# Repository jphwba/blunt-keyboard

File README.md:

# Blunt-Keyboard

This keyboard is a 75% keyboard which has a magnetically attatchable numpad to it. It uses a raspberry pi pico rp2040 as the microcontroller for the main keyboard while using a xiao seeed studio rp2040 as the microcontroller for the numpad. This would connect via two usb C cables into my pc. I made this because I really need a new keyboard since my current one cant even play games anymore due to some weird bug in the pcb where it just randomly spams keys, plus I've had it for almost 10 years.

## Assembly
On the main part of the keyboard, the pcb is mounted using five mounting holes on the pcb and five standoffs on the base where M2 heatset inserts will sit. On top of these standoffs will go the PCB where it will be screwed into the base. Then the top goes ontop of the pcb/base walls. This is connected via screws going from the bottom to the top
The numpad however is screwed in with the threads in the 3d print. This was not a great design choice at the time as I wasn't as experienced with how 3d printers work but I will take the gamble and if it doesn't work I am able to use tape. HOWEVER the pcb is screwed into the base using the same heatset inserts so the pcb will be secured. The key plate is attatched to the top cover with a joint (i forgot the name).
For the magnetic attatchements, two 7mm magnets go in two the 7mm wide holes on BOTH the numpad and the main keyboard and is attatched to each part with some basic super glue. With this the two devices can seamlessly attatch and detach. The two components also have seperate microcontrollers, meaning two different usb connections into my pc. I chose this over having the numpad atatch into the main keyboard for first simple firmware and schematic design but also because it means I have a portable numpad.

### Numpad Render

### Main Keyboard Render

### Full Assembled Render

### PCB Layout Pad

### Pad Schematic

### Main PCB Layout

### Main Schematic

### Main PCB Order

### PAD PCB Order

### BOM
|Item                                                                                                                                                                          |Qty|Price (AUD)|Site                                                                                                                                                                                                                                                                                                                                                                                                                                                                                                                                                                                                                                 |
|------------------------------------------------------------------------------------------------------------------------------------------------------------------------------|---|-----------|-------------------------------------------------------------------------------------------------------------------------------------------------------------------------------------------------------------------------------------------------------------------------------------------------------------------------------------------------------------------------------------------------------------------------------------------------------------------------------------------------------------------------------------------------------------------------------------------------------------------------------------|
|DUROCK Plate Mount Stabilizers V3, Innovative Pre-clipped Stem for Minimum Wire Wobble 2U 6.25U 7U Plate Keyboard Stabilizers V3 (Color: V3 BS 4x2u 1x6.25u)                  |1  |$11.39     |https://www.aliexpress.com/item/1005006528731543.html?spm=a2g0o.cart.0.0.4c3438dal21w6q&mp=1&pdp_npi=6%40dis%21AUD%21AUD+11.39%21AUD+11.39%21%21AUD+11.39%21%21%21%402103129017855613570607710e1021%2112000037543723481%21ct%21AU%21-1%21%211%210%21&pdp_ext_f=%7B%22cart2PdpParams%22%3A%7B%22pdpBusinessMode%22%3A%22retail%22%7D%7D                                                                                                                                                                                                                                                                                               |
|110Pcs Outemu Switches for Mechanical Keyboard 3Pin Clicky Linear Tactile Silent Switch RGB LED SMD Gaming Mechan with MX Switch (Color: 110p DustProof Brown)                |1  |$43.46     |https://www.aliexpress.com/item/1005011976942889.html?spm=a2g0o.cart.0.0.4c3438dal21w6q&mp=1&pdp_npi=6%40dis%21AUD%21AUD+43.46%21AUD+3.08%21%21AUD+3.08%21%21%21%402103129017855613570607710e1021%2112000057186154978%21ct%21AU%21-1%21%211%210%21                                                                                                                                                                                                                                                                                                                                                                                   |
|100pcs/lot 1N4148W T4 BAV21W T3 SOD-123 1N4148WS BAV21WS SOD-323 1N4148WT SOD-523 1N4148 BAV21 BAV21W SMD Switching Diodes (Color: 1N4148W T4 SOD-123)                        |1  |$3.72      |https://www.aliexpress.com/item/1005007160563285.html?spm=a2g0o.cart.0.0.4c3438dal21w6q&mp=1&pdp_npi=6%40dis%21AUD%21AUD+3.72%21AUD+2.27%21%21AUD+2.27%21%21%21%402103129017855613570607710e1021%2112000039653324544%21ct%21AU%21-1%21%211%210%21                                                                                                                                                                                                                                                                                                                                                                                    |
|Original Raspberry Pi Pico Development Board,Pico or Pico H with Pin Header, support MciroPython/C++                                                                          |1  |$9.78      |https://www.aliexpress.com/item/1005008714908011.html?spm=a2g0o.cart.0.0.4c3438dal21w6q&mp=1&pdp_npi=6%40dis%21AUD%21AUD+9.78%21AUD+4.79%21%21AUD+4.79%21%21%21%402103129017855613570607710e1021%2112000046359830441%21ct%21AU%21-1%21%211%210%21                                                                                                                                                                                                                                                                                                                                                                                    |
|100PCS SK6812MINI-E SK6812 MINI-E RGB 3228 LED chip SMD                                                                                                                       |1  |$14.24     |https://www.aliexpress.com/item/1005005956813491.html?spm=a2g0o.cart.0.0.2cd238daWuNwsJ&mp=1&pdp_npi=6%40dis%21AUD%21AUD+14.24%21AUD+13.39%21%21AUD+13.39%21%21%21%40210328df17855654955145397e10b6%2112000035024278716%21ct%21AU%21-1%21%211%210%21                                                                                                                                                                                                                                                                                                                                                                                 |
|XVX 119 Keys Black Transparent PC Keycaps 60/68/75/87/98/100 Mechanical Keyboard Key Cap Crystal Clear Keycaps for Gaming/Office (Color: black)                               |1  |$30.84     |https://www.aliexpress.com/item/1005010587844811.html?spm=a2g0o.cart.0.0.675938daAlDdi5&mp=1&pdp_npi=6%40dis%21AUD%21AUD+30.95%21AUD+22.59%21%21AUD+22.59%21%21%21%40210328df17855662600466416e0d9f%2112000052907539638%21ct%21AU%21-1%21%211%210%21                                                                                                                                                                                                                                                                                                                                                                                 |
|50pcs 5-30mm Anti-slip Black Self Adhesive Round Silicone Rubber Feet Pad Laptops Keyboards Calculators Monitors Anti-skid Pads (Size: OD 15mm, Color: Thick 0.5mm)           |1  |$3.25      |https://www.aliexpress.com/item/1005012365785428.html?spm=a2g0o.productlist.main.9.4de19oaH9oaHuB&algo_pvid=cd5a83e3-1229-4647-a495-e3f16f297cca&algo_exp_id=cd5a83e3-1229-4647-a495-e3f16f297cca-8&pdp_ext_f=%7B%22order%22%3A%2210%22%2C%22eval%22%3A%221%22%2C%22fromPage%22%3A%22search%22%7D&pdp_npi=6%40dis%21AUD%212.31%212.31%21%21%211.60%211.60%21%4021030f4a17855681020947549e1149%2112000058187329086%21sea%21AU%210%21ABX%211%210%21n_tag%3A-29910%3Bd%3Aa8aafb62%3Bm03_new_user%3A-29895&curPageLogUid=XU7lr6tnileh&utparam-url=scene%3Asearch%7Cquery_from%3A%7Cx_object_id%3A1005012365785428%7C_p_origin_prod%3A    |
|10/15/20/40/50/100pcs M1 M1.2 M1.4 M2 M2.5 M3 M4 M5 M6 M8 Thread Knurled Brass Heat Insert Nut Copper Embedment Embed Parts Nuts (Size: M2x3.5mm (50pcs), Color: Length 3.5mm)|1  |$3.87      |https://www.aliexpress.com/item/1005007424930348.html?spm=a2g0o.productlist.main.1.5d47dkVRdkVRFI&algo_pvid=f3287ffa-e8c5-45b6-be15-06364e1b8824&algo_exp_id=f3287ffa-e8c5-45b6-be15-06364e1b8824-0&pdp_ext_f=%7B%22order%22%3A%224489%22%2C%22eval%22%3A%221%22%2C%22fromPage%22%3A%22search%22%7D&pdp_npi=6%40dis%21AUD%212.44%211.46%21%21%2111.44%216.86%21%402101d2e717859226917101841e10da%2112000040708235172%21sea%21AU%210%21ABX%211%210%21n_tag%3A-29910%3Bd%3Aa8aafb62%3Bm03_new_user%3A-29895&curPageLogUid=nWZkAVTMulic&utparam-url=scene%3Asearch%7Cquery_from%3A%7Cx_object_id%3A1005007424930348%7C_p_origin_prod%3A |
|7x3 mm Powerful Magnets 7mmx3mm Small Round Magnet 7x3mm For Home Refrigerators, Offices DIY 7*3 mm (Color: 20PCS, Size: 7x3mm)                                               |1  |$9.70      |https://www.aliexpress.com/item/1005009743408781.html?spm=a2g0o.cart.0.0.5a4038dapRSJXy&mp=1&pdp_npi=6%40dis%21AUD%21AUD+9.70%21AUD+6.89%21%21AUD+6.89%21%21%21%402101ca9517859231451535510e2109%2112000050016793430%21ct%21AU%21-1%21%211%210%21                                                                                                                                                                                                                                                                                                                                                                                    |
|Pad Specific                                                                                                                                                                  |   |           |                                                                                                                                                                                                                                                                                                                                                                                                                                                                                                                                                                                                                                     |
|(50pcs) 1N4148W T4 4148WS 4148WT SOD-123/SOD-323/SOD-523 SMD Switching Diodes (Color: 1N4148W T4 SOD123)                                                                      |1  |$0.88      |https://www.aliexpress.com/item/1005007406908801.html?spm=a2g0o.cart.0.0.2cd238daUQg641&mp=1&pdp_npi=6%40dis%21AUD%21AUD+0.88%21AUD+0.88%21%21AUD+0.88%21%21%21%40210328df17855654453944118e10b6%2112000044783709518%21ct%21AU%21-1%21%211%210%21                                                                                                                                                                                                                                                                                                                                                                                    |
|10pcs/1pc RP2040 Seeed XIAO Raspberry Pi Development Board Module For Arduino/MicroPython/CircuitPython (Model Number: 1pc)                                                   |1  |$10.70     |https://www.aliexpress.com/item/1005008200917480.html?spm=a2g0o.productlist.main.1.6ac5379cKx7D6w&algo_pvid=b6c6bc21-d979-4d64-972b-8bcf0e8f28f7&algo_exp_id=b6c6bc21-d979-4d64-972b-8bcf0e8f28f7-0&pdp_ext_f=%7B%22order%22%3A%22279%22%2C%22eval%22%3A%221%22%2C%22fromPage%22%3A%22search%22%7D&pdp_npi=6%40dis%21AUD%2120.56%2114.39%21%21%2114.23%219.96%21%402101e81117855657959013083e100a%2112000058130698584%21sea%21AU%210%21ABX%211%210%21n_tag%3A-29910%3Bd%3Aa8aafb62%3Bm03_new_user%3A-29895&curPageLogUid=Gb0bLHPVv7Jw&utparam-url=scene%3Asearch%7Cquery_from%3A%7Cx_object_id%3A1005008200917480%7C_p_origin_prod%3A|
|Printing-Legion                                                                                                                                                               |1  |$30.00     |                                                                                                                                                                                                                                                                                                                                                                                                                                                                                                                                                                                                                                     |
|Total                                                                                                                                                                         |   |$141.83    |                                                                                                                                                                                                                                                                                                                                                                                                                                                                                                                                                                                                                                     |

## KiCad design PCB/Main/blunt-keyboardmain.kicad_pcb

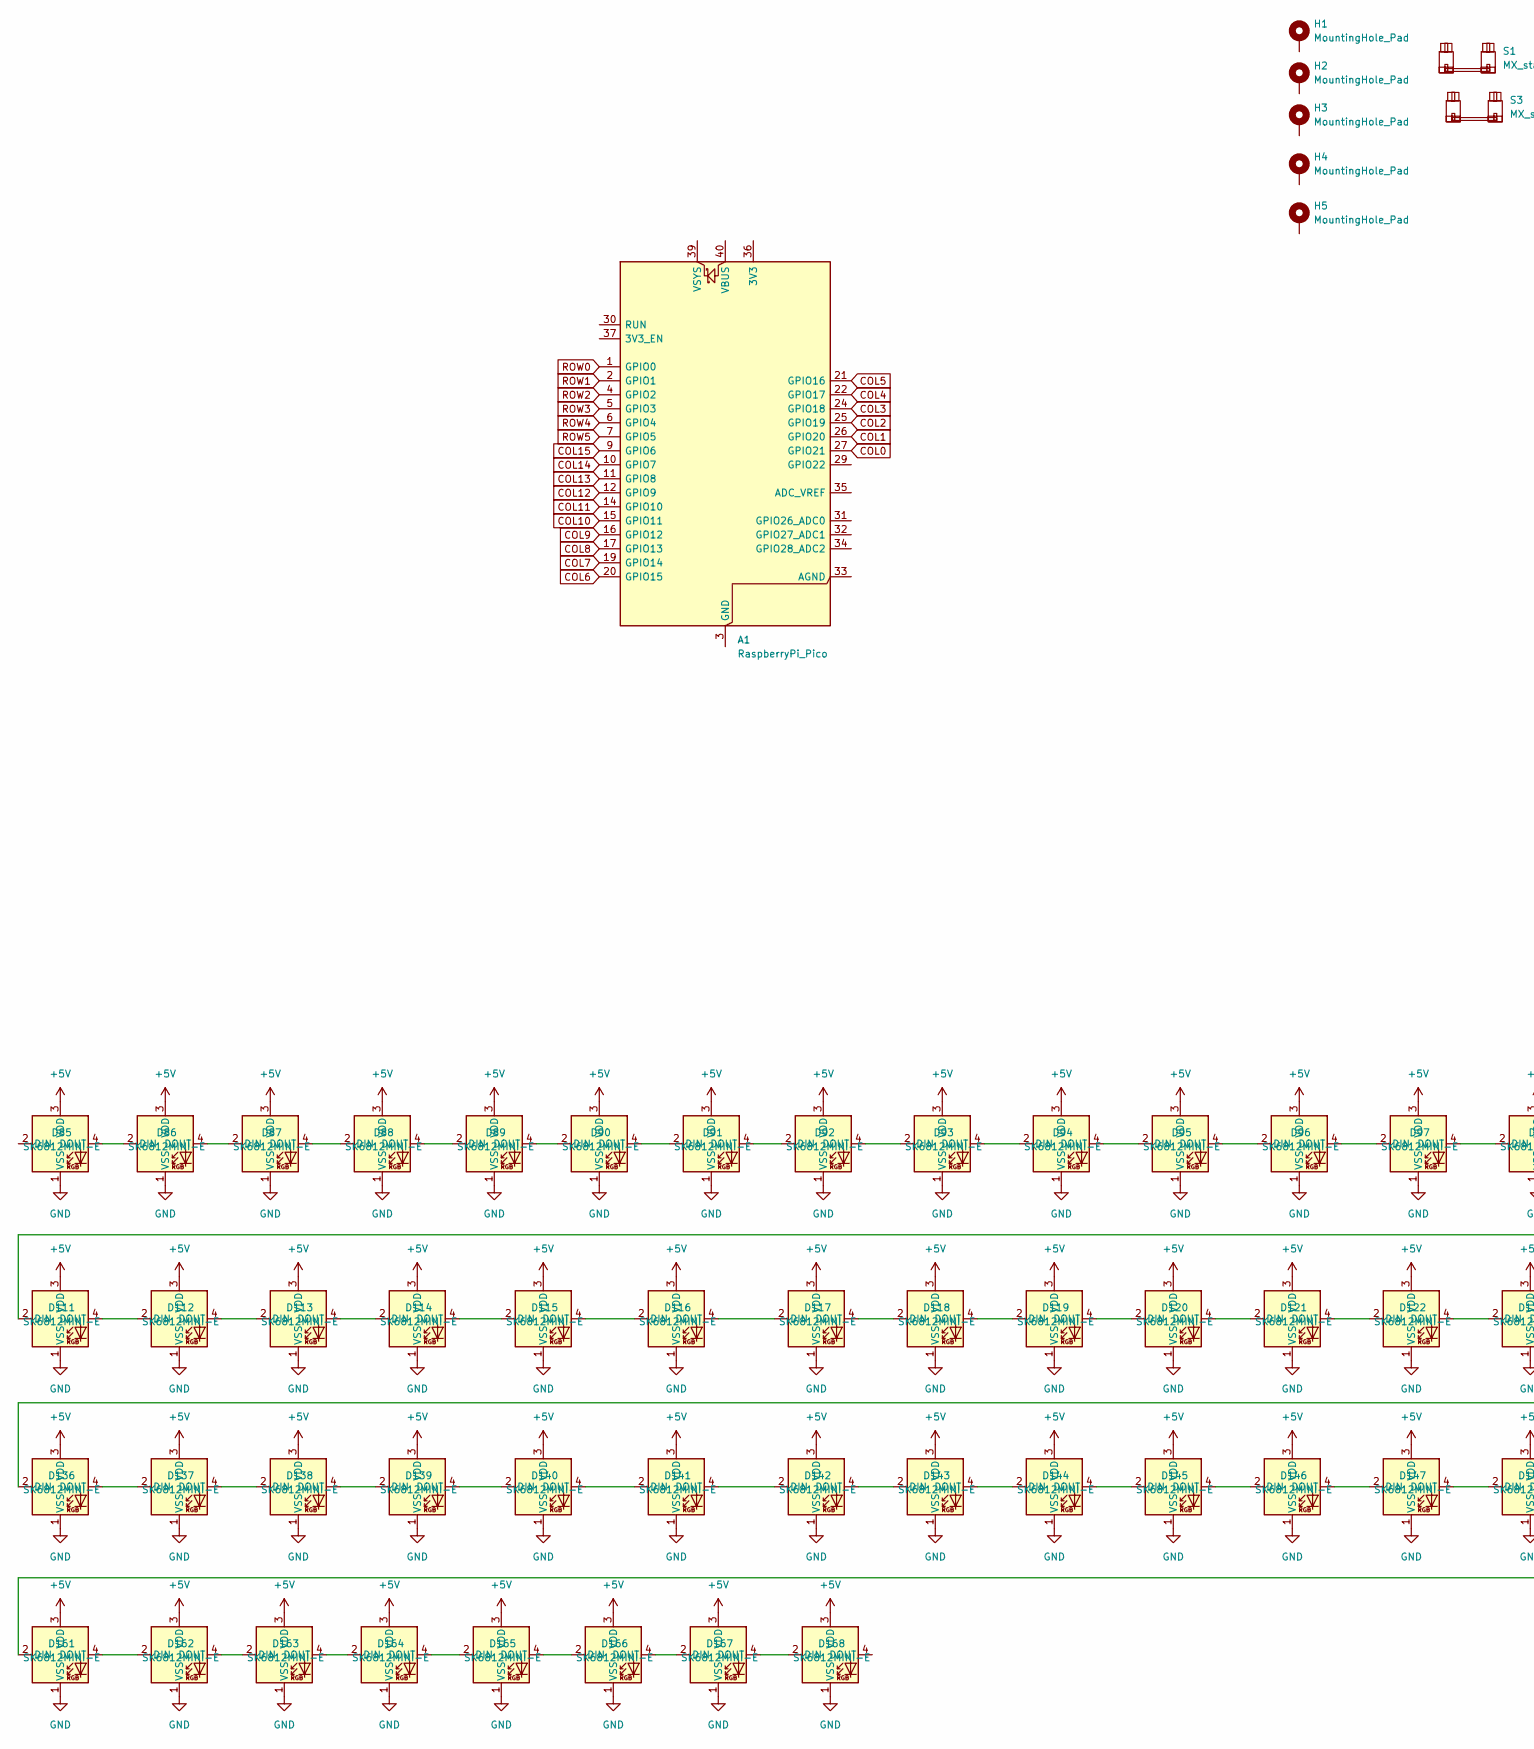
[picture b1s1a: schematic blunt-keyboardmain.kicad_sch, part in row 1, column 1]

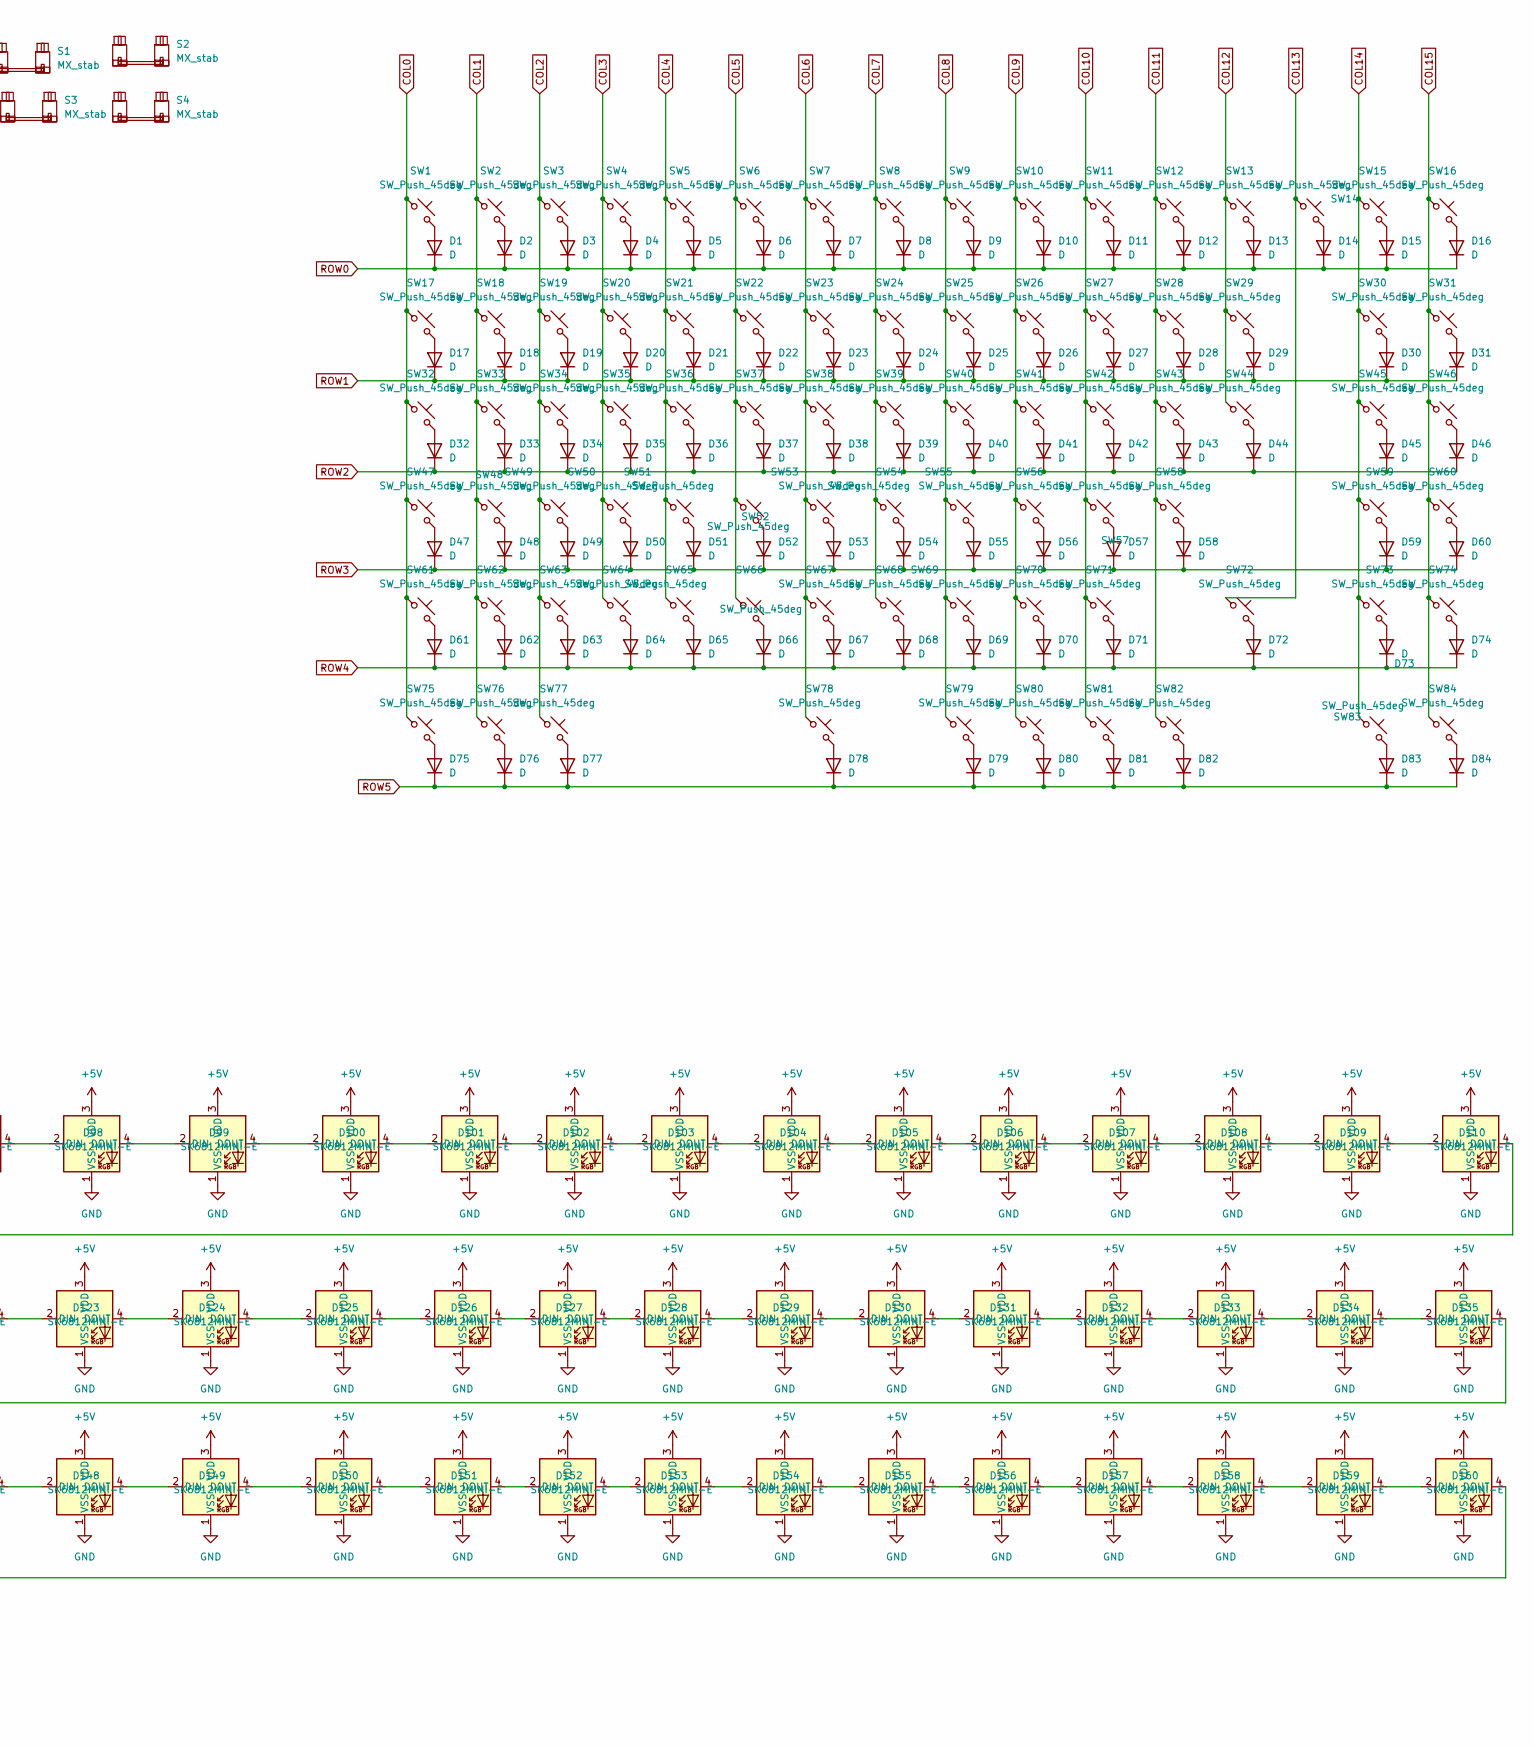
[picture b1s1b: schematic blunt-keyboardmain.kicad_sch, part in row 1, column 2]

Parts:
A1: RaspberryPi_Pico; RaspberryPi_Pico_Common_Unspecified
D1, D2, D3, D4, D5, D6, D7, D8, D9, D10, D11, D12, D13, D14, D15, D16, D17, D18, D19, D20, D21, D22, D23, D24, D25, D26, D27, D28, D29, D30, D31, D32, D33, D34, D35, D36, D37, D38, D39, D40, D41, D42, D43, D44, D45, D46, D47, D48, D49, D50, D51, D52, D53, D54, D55, D56, D57, D58, D59, D60, D61, D62, D63, D64, D65, D66, D67, D68, D69, D70, D71, D72, D73, D74, D75, D76, D77, D78, D79, D80, D81, D82, D83, D84: D; D_SOD-123
D85, D86, D87, D88, D89, D90, D91, D92, D93, D94, D95, D96, D97, D98, D99, D100, D101, D102, D103, D104, D105, D106, D107, D108, D109, D110, D111, D112, D113, D114, D115, D116, D117, D118, D119, D120, D121, D122, D123, D124, D125, D126, D127, D128, D129, D130, D131, D132, D133, D134, D135, D136, D137, D138, D139, D140, D141, D142, D143, D144, D145, D146, D147, D148, D149, D150, D151, D152, D153, D154, D155, D156, D157, D158, D159, D160, D161, D162, D163, D164, D165, D166, D167, D168: SK6812MINI-E; LED_SK6812MINI-E_3.2x2.8mm_P1.5mm_ReverseMount
H1, H2, H3, H4, H5: MountingHole_Pad; MountingHole_2.2mm_M2_ISO7380_Pad
S1: MX_stab; STAB_MX_P_6.25u
S2, S4: MX_stab; STAB_MX_P_2.25u
S3: MX_stab; STAB_MX_P_2u
SW1, SW2, SW3, SW4, SW5, SW6, SW7, SW8, SW9, SW10, SW11, SW12, SW13, SW14, SW15, SW16, SW17, SW18, SW19, SW20, SW21, SW22, SW23, SW24, SW25, SW26, SW27, SW28, SW29, SW30, SW31, SW33, SW34, SW35, SW36, SW37, SW38, SW39, SW40, SW41, SW42, SW43, SW44, SW46, SW48, SW49, SW50, SW51, SW52, SW53, SW54, SW55, SW56, SW57, SW58, SW60, SW61, SW62, SW63, SW64, SW65, SW66, SW67, SW68, SW69, SW70, SW71, SW73, SW74, SW78, SW79, SW80, SW81, SW82, SW83, SW84: SW_Push_45deg; SW_Matias_1.00u
SW32, SW45: SW_Push_45deg; SW_Matias_1.50u
SW47, SW72: SW_Push_45deg; SW_Matias_1.75u
SW59: SW_Push_45deg; SW_Matias_2.25u
SW75, SW76, SW77: SW_Push_45deg; SW_Matias_1.25u

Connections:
+5V: D85.3 (VDD), D86.3 (VDD), D87.3 (VDD), D88.3 (VDD), D89.3 (VDD), D90.3 (VDD), D91.3 (VDD), D92.3 (VDD), D93.3 (VDD), D94.3 (VDD), D95.3 (VDD), D96.3 (VDD), D97.3 (VDD), D98.3 (VDD), D99.3 (VDD), D100.3 (VDD), D101.3 (VDD), D102.3 (VDD), D103.3 (VDD), D104.3 (VDD), D105.3 (VDD), D106.3 (VDD), D107.3 (VDD), D108.3 (VDD), D109.3 (VDD), D110.3 (VDD), D111.3 (VDD), D112.3 (VDD), D113.3 (VDD), D114.3 (VDD), D115.3 (VDD), D116.3 (VDD), D117.3 (VDD), D118.3 (VDD), D119.3 (VDD), D120.3 (VDD), D121.3 (VDD), D122.3 (VDD), D123.3 (VDD), D124.3 (VDD), D125.3 (VDD), D126.3 (VDD), D127.3 (VDD), D128.3 (VDD), D129.3 (VDD), D130.3 (VDD), D131.3 (VDD), D132.3 (VDD), D133.3 (VDD), D134.3 (VDD), D135.3 (VDD), D136.3 (VDD), D137.3 (VDD), D138.3 (VDD), D139.3 (VDD), D140.3 (VDD), D141.3 (VDD), D142.3 (VDD), D143.3 (VDD), D144.3 (VDD), D145.3 (VDD), D146.3 (VDD), D147.3 (VDD), D148.3 (VDD), D149.3 (VDD), D150.3 (VDD), D151.3 (VDD), D152.3 (VDD), D153.3 (VDD), D154.3 (VDD), D155.3 (VDD), D156.3 (VDD), D157.3 (VDD), D158.3 (VDD), D159.3 (VDD), D160.3 (VDD), D161.3 (VDD), D162.3 (VDD), D163.3 (VDD), D164.3 (VDD), D165.3 (VDD), D166.3 (VDD), D167.3 (VDD), D168.3 (VDD)
COL0: A1.27 (GPIO21), SW1.1, SW17.1, SW32.1, SW47.1, SW61.1, SW75.1
COL1: A1.26 (GPIO20), SW2.1, SW18.1, SW33.1, SW48.1, SW62.1, SW76.1
COL2: A1.25 (GPIO19), SW3.1, SW19.1, SW34.1, SW49.1, SW63.1, SW77.1
COL3: A1.24 (GPIO18), SW4.1, SW20.1, SW35.1, SW50.1, SW64.1
COL4: A1.22 (GPIO17), SW5.1, SW21.1, SW36.1, SW51.1, SW65.1
COL5: A1.21 (GPIO16), SW6.1, SW22.1, SW37.1, SW52.1, SW66.1
COL6: A1.20 (GPIO15), SW7.1, SW23.1, SW38.1, SW53.1, SW67.1, SW78.1
COL7: A1.19 (GPIO14), SW8.1, SW24.1, SW39.1, SW54.1, SW68.1
COL8: A1.17 (GPIO13), SW9.1, SW25.1, SW40.1, SW55.1, SW69.1, SW79.1
COL9: A1.16 (GPIO12), SW10.1, SW26.1, SW41.1, SW56.1, SW70.1, SW80.1
COL10: A1.15 (GPIO11), SW11.1, SW27.1, SW42.1, SW57.1, SW71.1, SW81.1
COL11: A1.14 (GPIO10), SW12.1, SW28.1, SW43.1, SW58.1, SW82.1
COL12: A1.12 (GPIO9), SW13.1, SW29.1, SW44.1
COL13: A1.11 (GPIO8), SW14.1, SW72.1
COL14: A1.10 (GPIO7), SW15.1, SW30.1, SW45.1, SW59.1, SW73.1, SW83.1
COL15: A1.9 (GPIO6), SW16.1, SW31.1, SW46.1, SW60.1, SW74.1, SW84.1
GND: D85.1 (VSS), D86.1 (VSS), D87.1 (VSS), D88.1 (VSS), D89.1 (VSS), D90.1 (VSS), D91.1 (VSS), D92.1 (VSS), D93.1 (VSS), D94.1 (VSS), D95.1 (VSS), D96.1 (VSS), D97.1 (VSS), D98.1 (VSS), D99.1 (VSS), D100.1 (VSS), D101.1 (VSS), D102.1 (VSS), D103.1 (VSS), D104.1 (VSS), D105.1 (VSS), D106.1 (VSS), D107.1 (VSS), D108.1 (VSS), D109.1 (VSS), D110.1 (VSS), D111.1 (VSS), D112.1 (VSS), D113.1 (VSS), D114.1 (VSS), D115.1 (VSS), D116.1 (VSS), D117.1 (VSS), D118.1 (VSS), D119.1 (VSS), D120.1 (VSS), D121.1 (VSS), D122.1 (VSS), D123.1 (VSS), D124.1 (VSS), D125.1 (VSS), D126.1 (VSS), D127.1 (VSS), D128.1 (VSS), D129.1 (VSS), D130.1 (VSS), D131.1 (VSS), D132.1 (VSS), D133.1 (VSS), D134.1 (VSS), D135.1 (VSS), D136.1 (VSS), D137.1 (VSS), D138.1 (VSS), D139.1 (VSS), D140.1 (VSS), D141.1 (VSS), D142.1 (VSS), D143.1 (VSS), D144.1 (VSS), D145.1 (VSS), D146.1 (VSS), D147.1 (VSS), D148.1 (VSS), D149.1 (VSS), D150.1 (VSS), D151.1 (VSS), D152.1 (VSS), D153.1 (VSS), D154.1 (VSS), D155.1 (VSS), D156.1 (VSS), D157.1 (VSS), D158.1 (VSS), D159.1 (VSS), D160.1 (VSS), D161.1 (VSS), D162.1 (VSS), D163.1 (VSS), D164.1 (VSS), D165.1 (VSS), D166.1 (VSS), D167.1 (VSS), D168.1 (VSS)
unnamed: A1.3 (GND), A1.8 (GND), A1.13 (GND), A1.18 (GND), A1.23 (GND), A1.28 (GND), A1.38 (GND)
unnamed: D1.2 (A), SW1.2
unnamed: D2.2 (A), SW2.2
unnamed: D3.2 (A), SW3.2
unnamed: D4.2 (A), SW4.2
unnamed: D5.2 (A), SW5.2
unnamed: D6.2 (A), SW6.2
unnamed: D7.2 (A), SW7.2
unnamed: D8.2 (A), SW8.2
unnamed: D9.2 (A), SW9.2
unnamed: D10.2 (A), SW10.2
unnamed: D11.2 (A), SW11.2
unnamed: D12.2 (A), SW12.2
unnamed: D13.2 (A), SW13.2
unnamed: D14.2 (A), SW14.2
unnamed: D15.2 (A), SW15.2
unnamed: D16.2 (A), SW16.2
unnamed: D17.2 (A), SW17.2
unnamed: D18.2 (A), SW18.2
unnamed: D19.2 (A), SW19.2
unnamed: D20.2 (A), SW20.2
unnamed: D21.2 (A), SW21.2
unnamed: D22.2 (A), SW22.2
unnamed: D23.2 (A), SW23.2
unnamed: D24.2 (A), SW24.2
unnamed: D25.2 (A), SW25.2
unnamed: D26.2 (A), SW26.2
unnamed: D27.2 (A), SW27.2
unnamed: D28.2 (A), SW28.2
unnamed: D29.2 (A), SW29.2
unnamed: D30.2 (A), SW30.2
unnamed: D31.2 (A), SW31.2
unnamed: D32.2 (A), SW32.2
unnamed: D33.2 (A), SW33.2
unnamed: D34.2 (A), SW34.2
unnamed: D35.2 (A), SW35.2
unnamed: D36.2 (A), SW36.2
unnamed: D37.2 (A), SW37.2
unnamed: D38.2 (A), SW38.2
unnamed: D39.2 (A), SW39.2
unnamed: D40.2 (A), SW40.2
unnamed: D41.2 (A), SW41.2
unnamed: D42.2 (A), SW42.2
unnamed: D43.2 (A), SW43.2
unnamed: D44.2 (A), SW44.2
unnamed: D45.2 (A), SW45.2
unnamed: D46.2 (A), SW46.2
unnamed: D47.2 (A), SW47.2
unnamed: D48.2 (A), SW48.2
unnamed: D49.2 (A), SW49.2
unnamed: D50.2 (A), SW50.2
unnamed: D51.2 (A), SW51.2
unnamed: D52.2 (A), SW52.2
unnamed: D53.2 (A), SW53.2
unnamed: D54.2 (A), SW54.2
unnamed: D55.2 (A), SW55.2
unnamed: D56.2 (A), SW56.2
unnamed: D57.2 (A), SW57.2
unnamed: D58.2 (A), SW58.2
unnamed: D59.2 (A), SW59.2
unnamed: D60.2 (A), SW60.2
unnamed: D61.2 (A), SW61.2
unnamed: D62.2 (A), SW62.2
unnamed: D63.2 (A), SW63.2
unnamed: D64.2 (A), SW64.2
unnamed: D65.2 (A), SW65.2
unnamed: D66.2 (A), SW66.2
unnamed: D67.2 (A), SW67.2
unnamed: D68.2 (A), SW68.2
unnamed: D69.2 (A), SW69.2
unnamed: D70.2 (A), SW70.2
unnamed: D71.2 (A), SW71.2
unnamed: D72.2 (A), SW72.2
unnamed: D73.2 (A), SW73.2
unnamed: D74.2 (A), SW74.2
unnamed: D75.2 (A), SW75.2
unnamed: D76.2 (A), SW76.2
unnamed: D77.2 (A), SW77.2
unnamed: D78.2 (A), SW78.2
unnamed: D79.2 (A), SW79.2
unnamed: D80.2 (A), SW80.2
unnamed: D81.2 (A), SW81.2
unnamed: D82.2 (A), SW82.2
unnamed: D83.2 (A), SW83.2
unnamed: D84.2 (A), SW84.2
unnamed: D85.4 (DOUT), D86.2 (DIN)
unnamed: D86.4 (DOUT), D87.2 (DIN)
unnamed: D87.4 (DOUT), D88.2 (DIN)
unnamed: D88.4 (DOUT), D89.2 (DIN)
unnamed: D89.4 (DOUT), D90.2 (DIN)
unnamed: D90.4 (DOUT), D91.2 (DIN)
unnamed: D91.4 (DOUT), D92.2 (DIN)
unnamed: D92.4 (DOUT), D93.2 (DIN)
unnamed: D93.4 (DOUT), D94.2 (DIN)
unnamed: D94.4 (DOUT), D95.2 (DIN)
unnamed: D95.4 (DOUT), D96.2 (DIN)
unnamed: D96.4 (DOUT), D97.2 (DIN)
unnamed: D97.4 (DOUT), D98.2 (DIN)
unnamed: D98.4 (DOUT), D99.2 (DIN)
unnamed: D99.4 (DOUT), D100.2 (DIN)
unnamed: D100.4 (DOUT), D101.2 (DIN)
unnamed: D101.4 (DOUT), D102.2 (DIN)
unnamed: D102.4 (DOUT), D103.2 (DIN)
unnamed: D103.4 (DOUT), D104.2 (DIN)
unnamed: D104.4 (DOUT), D105.2 (DIN)
unnamed: D105.4 (DOUT), D106.2 (DIN)
unnamed: D106.4 (DOUT), D107.2 (DIN)
unnamed: D107.4 (DOUT), D108.2 (DIN)
unnamed: D108.4 (DOUT), D109.2 (DIN)
unnamed: D109.4 (DOUT), D110.2 (DIN)
unnamed: D110.4 (DOUT), D111.2 (DIN)
unnamed: D111.4 (DOUT), D112.2 (DIN)
unnamed: D112.4 (DOUT), D113.2 (DIN)
unnamed: D113.4 (DOUT), D114.2 (DIN)
unnamed: D114.4 (DOUT), D115.2 (DIN)
unnamed: D115.4 (DOUT), D116.2 (DIN)
unnamed: D116.4 (DOUT), D117.2 (DIN)
unnamed: D117.4 (DOUT), D118.2 (DIN)
unnamed: D118.4 (DOUT), D119.2 (DIN)
unnamed: D119.4 (DOUT), D120.2 (DIN)
unnamed: D120.4 (DOUT), D121.2 (DIN)
unnamed: D121.4 (DOUT), D122.2 (DIN)
unnamed: D122.4 (DOUT), D123.2 (DIN)
unnamed: D123.4 (DOUT), D124.2 (DIN)
unnamed: D124.4 (DOUT), D125.2 (DIN)
unnamed: D125.4 (DOUT), D126.2 (DIN)
unnamed: D126.4 (DOUT), D127.2 (DIN)
unnamed: D127.4 (DOUT), D128.2 (DIN)
unnamed: D128.4 (DOUT), D129.2 (DIN)
unnamed: D129.4 (DOUT), D130.2 (DIN)
unnamed: D130.4 (DOUT), D131.2 (DIN)
unnamed: D131.4 (DOUT), D132.2 (DIN)
unnamed: D132.4 (DOUT), D133.2 (DIN)
unnamed: D133.4 (DOUT), D134.2 (DIN)
unnamed: D134.4 (DOUT), D135.2 (DIN)
unnamed: D135.4 (DOUT), D136.2 (DIN)
unnamed: D136.4 (DOUT), D137.2 (DIN)
unnamed: D137.4 (DOUT), D138.2 (DIN)
unnamed: D138.4 (DOUT), D139.2 (DIN)
unnamed: D139.4 (DOUT), D140.2 (DIN)
unnamed: D140.4 (DOUT), D141.2 (DIN)
unnamed: D141.4 (DOUT), D142.2 (DIN)
unnamed: D142.4 (DOUT), D143.2 (DIN)
unnamed: D143.4 (DOUT), D144.2 (DIN)
unnamed: D144.4 (DOUT), D145.2 (DIN)
unnamed: D145.4 (DOUT), D146.2 (DIN)
unnamed: D146.4 (DOUT), D147.2 (DIN)
unnamed: D147.4 (DOUT), D148.2 (DIN)
unnamed: D148.4 (DOUT), D149.2 (DIN)
unnamed: D149.4 (DOUT), D150.2 (DIN)
unnamed: D150.4 (DOUT), D151.2 (DIN)
unnamed: D151.4 (DOUT), D152.2 (DIN)
unnamed: D152.4 (DOUT), D153.2 (DIN)
unnamed: D153.4 (DOUT), D154.2 (DIN)
unnamed: D154.4 (DOUT), D155.2 (DIN)
unnamed: D155.4 (DOUT), D156.2 (DIN)
unnamed: D156.4 (DOUT), D157.2 (DIN)
unnamed: D157.4 (DOUT), D158.2 (DIN)
unnamed: D158.4 (DOUT), D159.2 (DIN)
unnamed: D159.4 (DOUT), D160.2 (DIN)
unnamed: D160.4 (DOUT), D161.2 (DIN)
unnamed: D161.4 (DOUT), D162.2 (DIN)
unnamed: D162.4 (DOUT), D163.2 (DIN)
unnamed: D163.4 (DOUT), D164.2 (DIN)
unnamed: D164.4 (DOUT), D165.2 (DIN)
unnamed: D165.4 (DOUT), D166.2 (DIN)
unnamed: D166.4 (DOUT), D167.2 (DIN)
unnamed: D167.4 (DOUT), D168.2 (DIN)
ROW0: A1.1 (GPIO0), D1.1 (K), D2.1 (K), D3.1 (K), D4.1 (K), D5.1 (K), D6.1 (K), D7.1 (K), D8.1 (K), D9.1 (K), D10.1 (K), D11.1 (K), D12.1 (K), D13.1 (K), D14.1 (K), D15.1 (K), D16.1 (K)
ROW1: A1.2 (GPIO1), D17.1 (K), D18.1 (K), D19.1 (K), D20.1 (K), D21.1 (K), D22.1 (K), D23.1 (K), D24.1 (K), D25.1 (K), D26.1 (K), D27.1 (K), D28.1 (K), D29.1 (K), D30.1 (K), D31.1 (K)
ROW2: A1.4 (GPIO2), D32.1 (K), D33.1 (K), D34.1 (K), D35.1 (K), D36.1 (K), D37.1 (K), D38.1 (K), D39.1 (K), D40.1 (K), D41.1 (K), D42.1 (K), D43.1 (K), D44.1 (K), D45.1 (K), D46.1 (K)
ROW3: A1.5 (GPIO3), D47.1 (K), D48.1 (K), D49.1 (K), D50.1 (K), D51.1 (K), D52.1 (K), D53.1 (K), D54.1 (K), D55.1 (K), D56.1 (K), D57.1 (K), D58.1 (K), D59.1 (K), D60.1 (K)
ROW4: A1.6 (GPIO4), D61.1 (K), D62.1 (K), D63.1 (K), D64.1 (K), D65.1 (K), D66.1 (K), D67.1 (K), D68.1 (K), D69.1 (K), D70.1 (K), D71.1 (K), D72.1 (K), D73.1 (K), D74.1 (K)
ROW5: A1.7 (GPIO5), D75.1 (K), D76.1 (K), D77.1 (K), D78.1 (K), D79.1 (K), D80.1 (K), D81.1 (K), D82.1 (K), D83.1 (K), D84.1 (K)

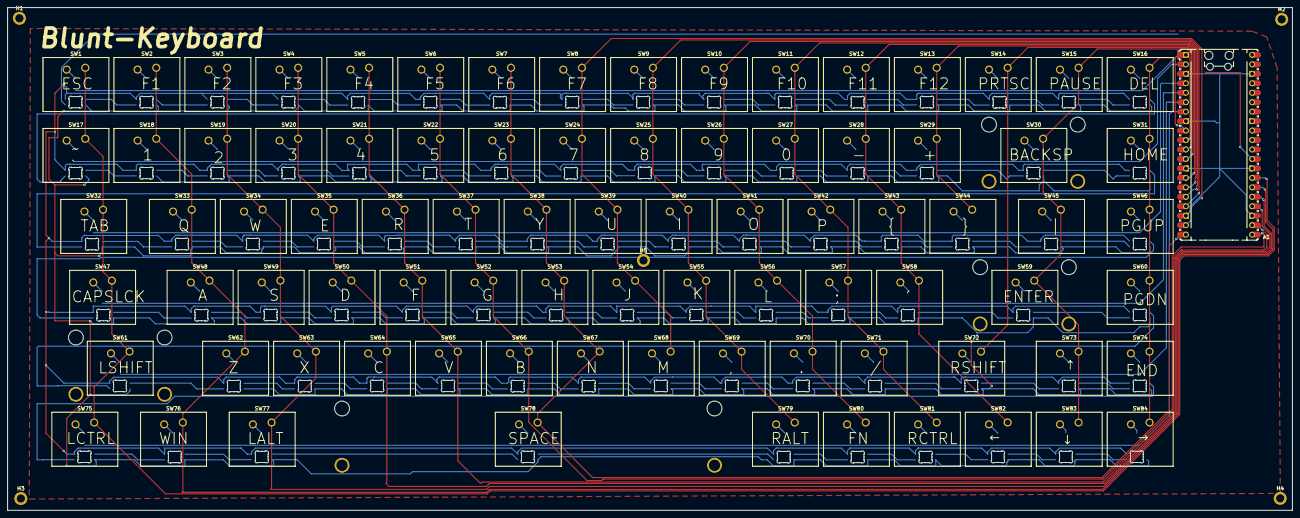
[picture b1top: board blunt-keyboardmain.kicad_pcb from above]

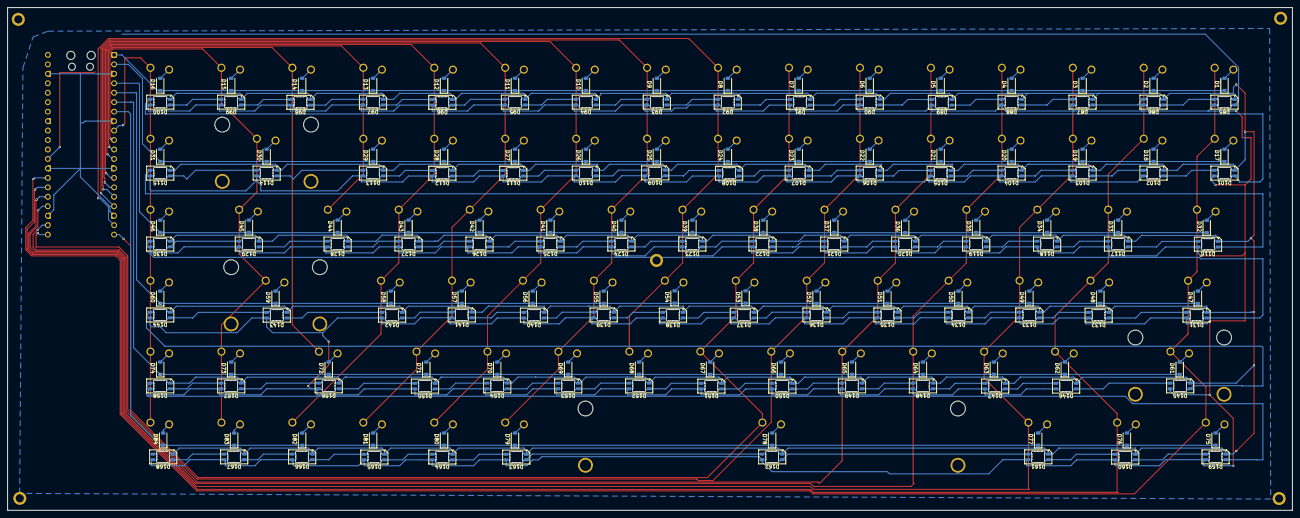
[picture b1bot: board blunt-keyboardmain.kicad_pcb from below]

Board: 2 copper layers, 345.0 x 135.0 mm, 262 parts (168 on the bottom side), 192 nets.
